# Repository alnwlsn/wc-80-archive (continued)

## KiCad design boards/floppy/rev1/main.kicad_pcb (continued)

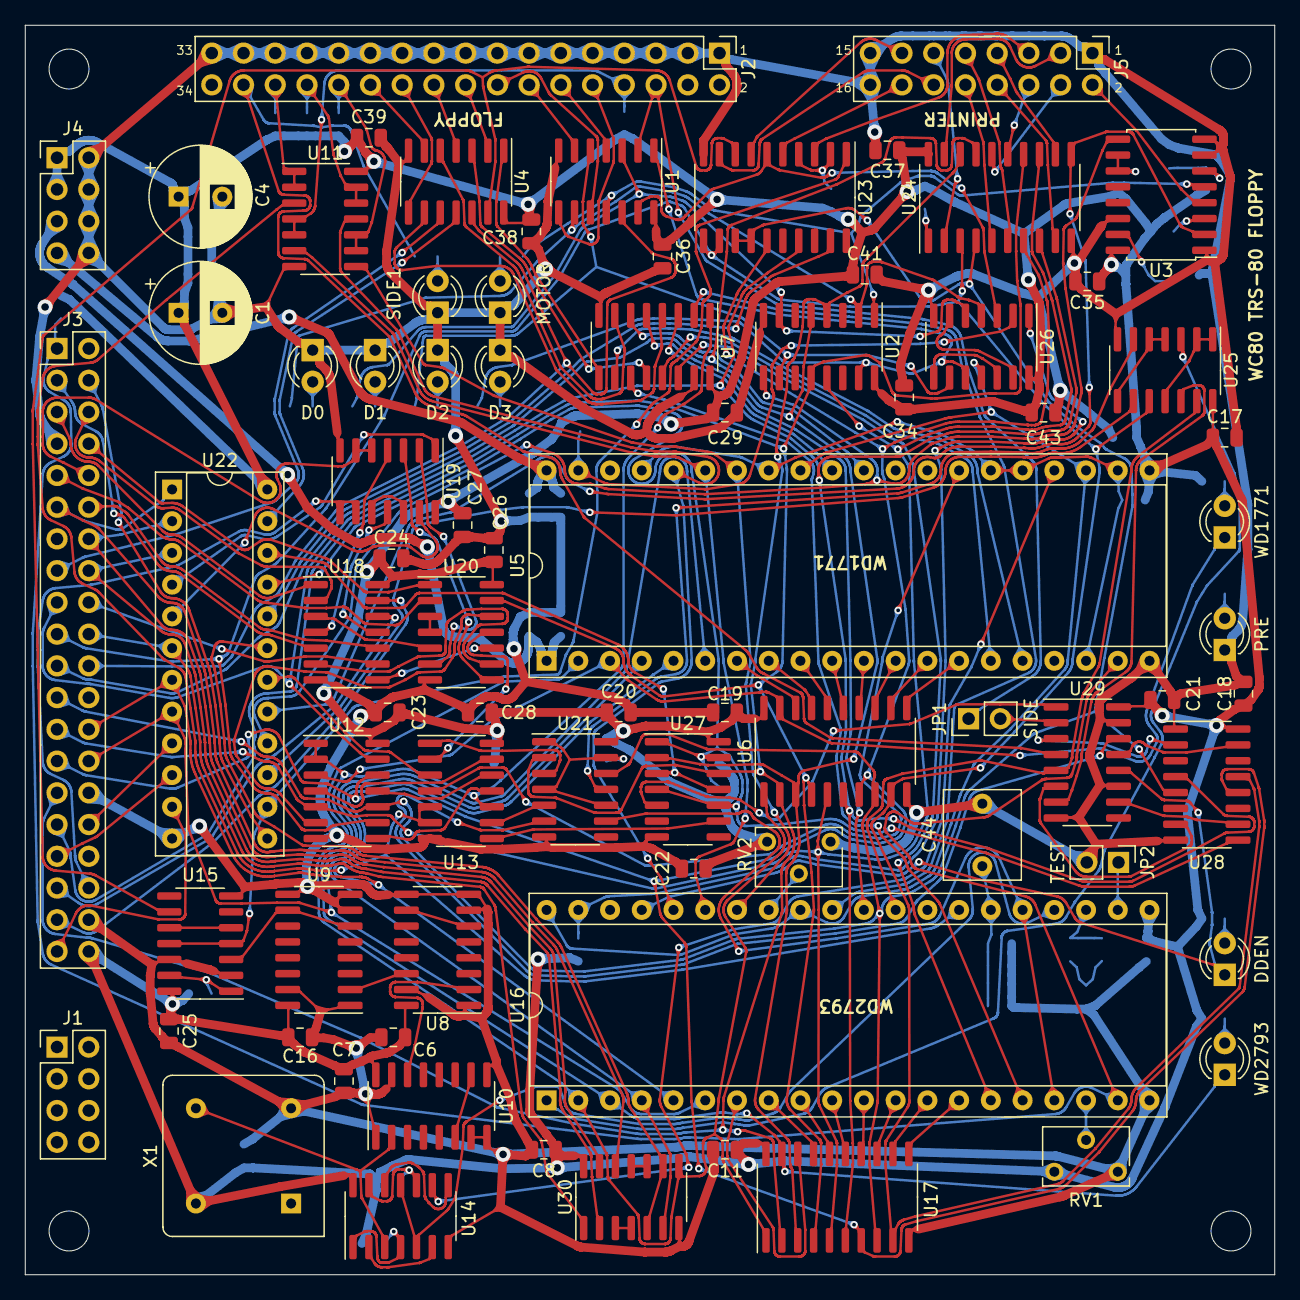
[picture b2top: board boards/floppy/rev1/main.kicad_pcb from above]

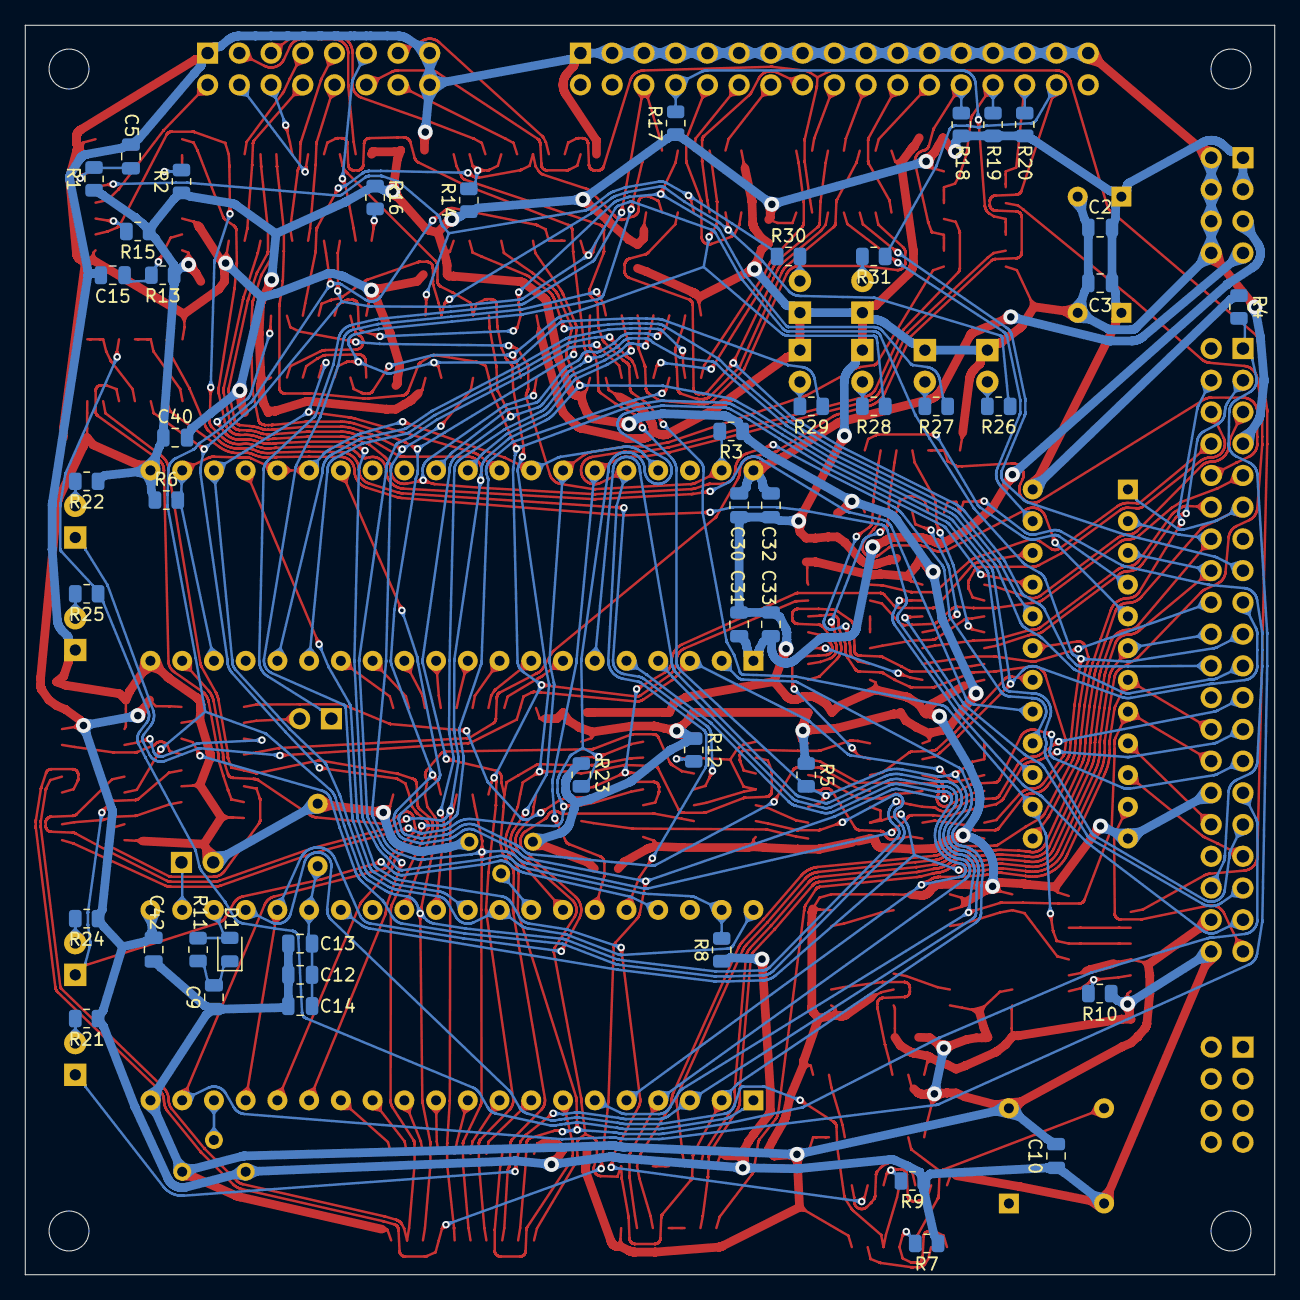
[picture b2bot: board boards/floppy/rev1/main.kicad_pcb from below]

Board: 2 copper layers, 100.0 x 100.0 mm, 130 parts (47 on the bottom side), 196 nets.

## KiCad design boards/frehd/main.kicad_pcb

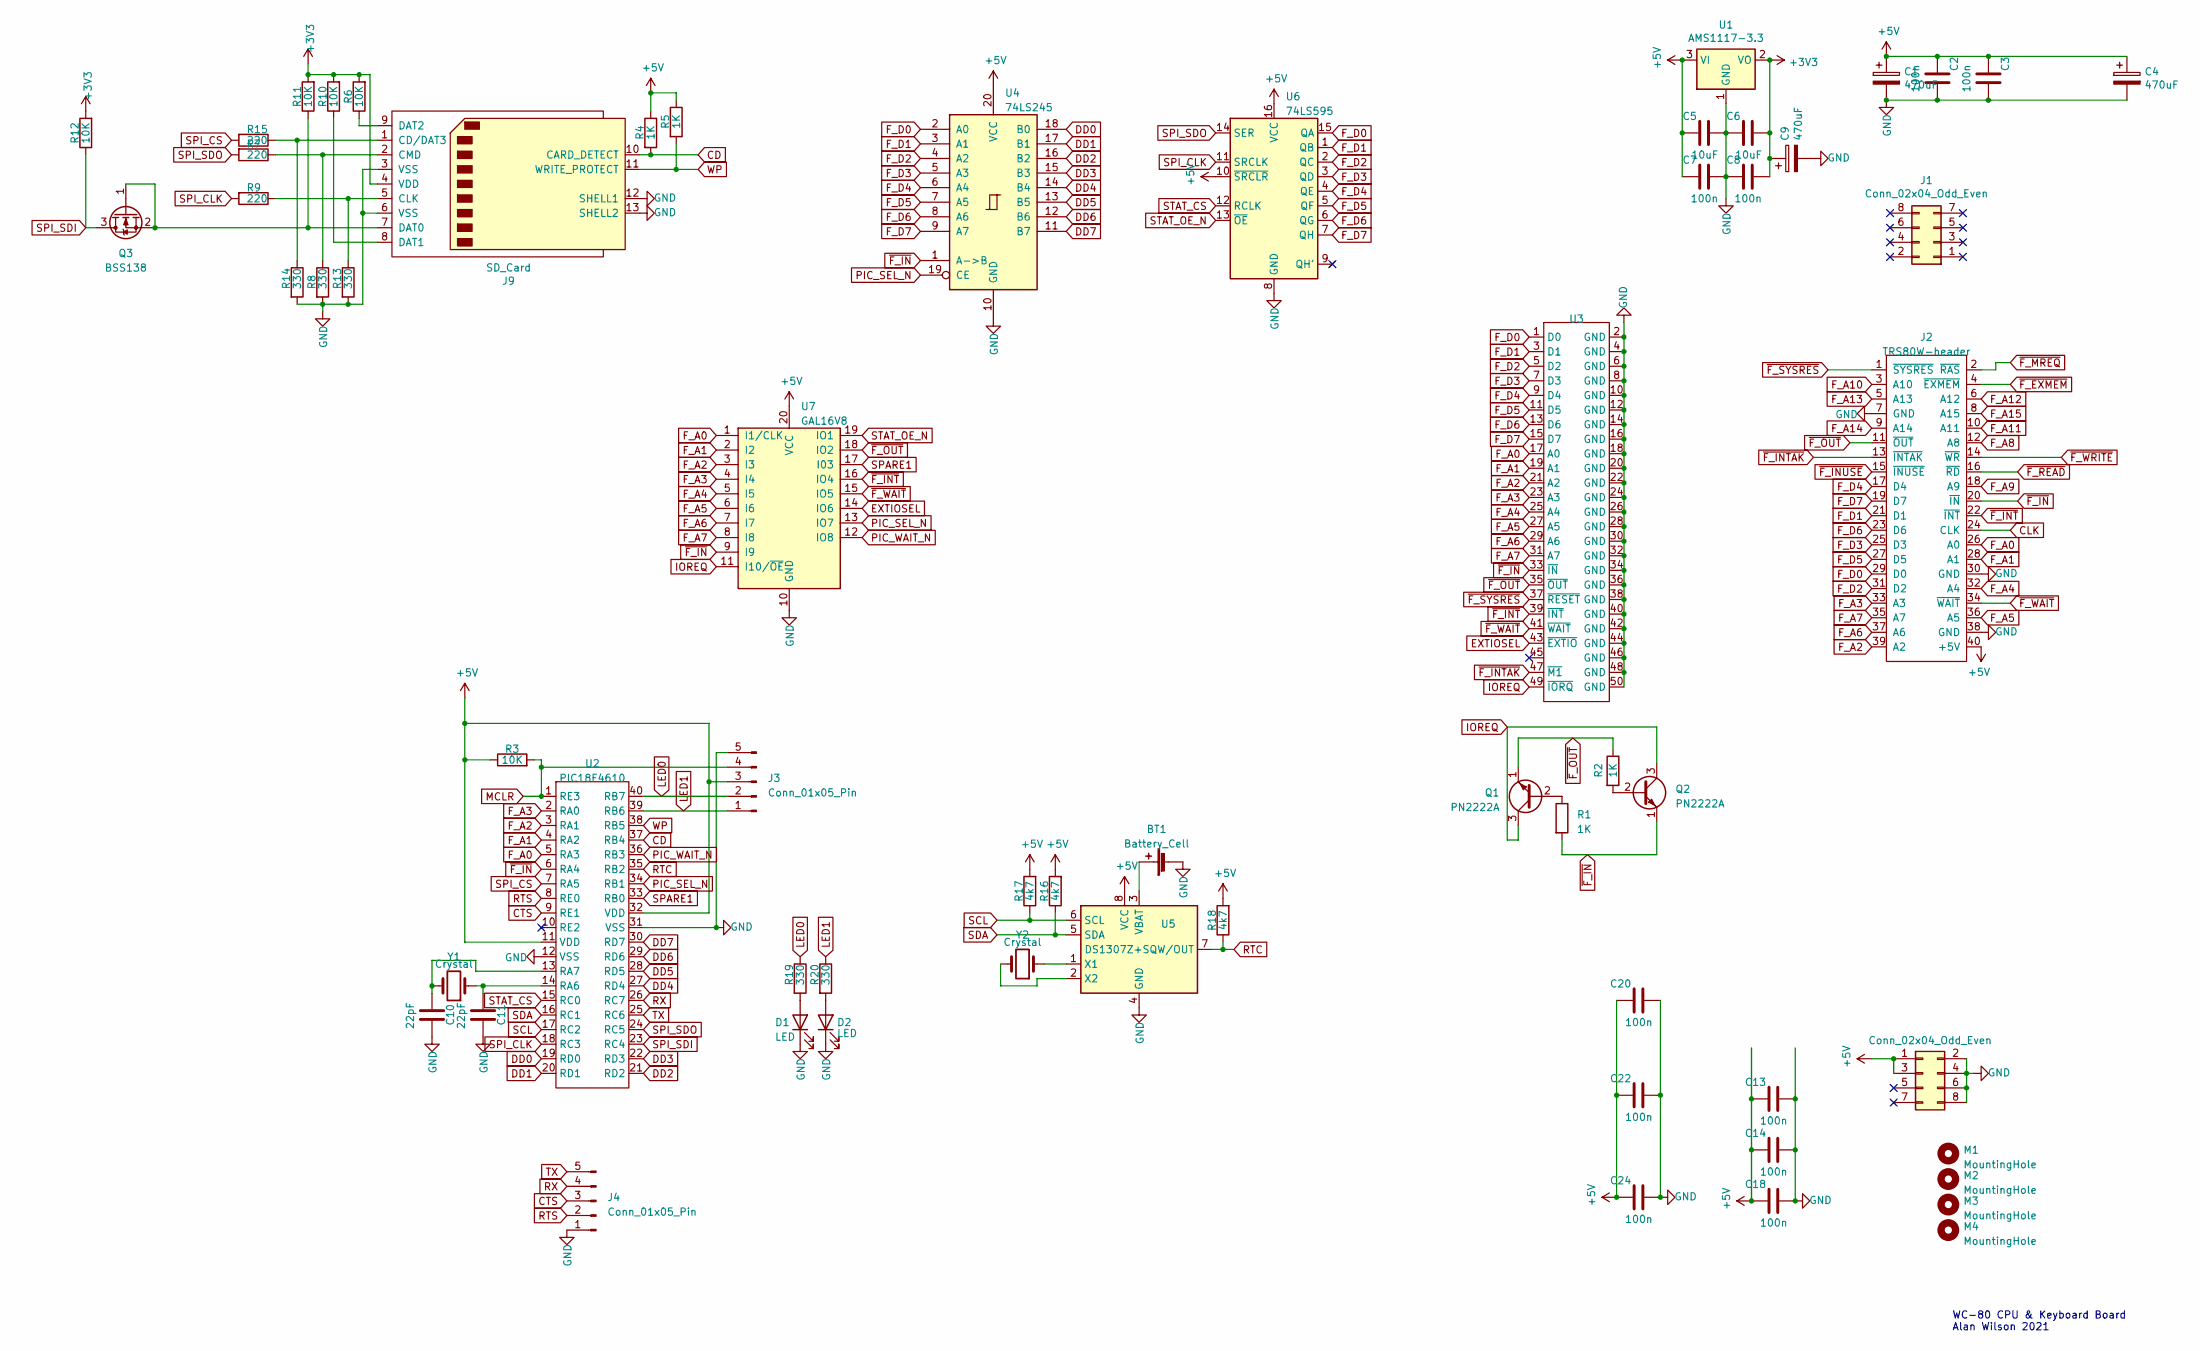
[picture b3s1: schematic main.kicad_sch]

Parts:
BT1: Battery_Cell; BS-01-A4CJ004
C1, C4, C9: 470uF; CP_Radial_D8.0mm_P3.50mm
C2, C3, C7, C8, C13, C14, C18, C20, C22, C24: 100n; C_0805_2012Metric
C5, C6: 10uF; C_0805_2012Metric
C10, C11: 22pF; C_0805_2012Metric
D1, D2: LED; LED_D3.0mm
J1, J5: Conn_02x04_Odd_Even; PinHeader_2x04_P2.54mm_Vertical
J2: TRS80W-header; PinHeader_2x20_P2.54mm_Vertical
J3, J4: Conn_01x05_Pin; PinSocket_1x05_P2.54mm_Vertical
J9: SD_Card; SD_Card_ XUNPU_SD-101
M1, M2, M3, M4: MountingHole; MountingHole_3.2mm_M3_DIN965
Q1, Q2: PN2222A; TO-92_Inline
Q3: BSS138; SOT-23
R1, R2, R4, R5: 1K; R_0805_2012Metric
R3, R6, R10, R11, R12: 10K; R_0805_2012Metric
R7, R9, R15: 220; R_0805_2012Metric
R8, R13, R14, R19, R20: 330; R_0805_2012Metric
R16, R17, R18: 4k7; R_0805_2012Metric
U1: AMS1117-3.3; SOT-223-3_TabPin2
U2: PIC18F4610; DIP-40_W15.24mm_Socket
U3: PinSocket_2x25_P2.54mm_Vertical
U4: 74LS245; SO-20_5.3x12.6mm_P1.27mm
U5: DS1307Z+; SOIC-8_3.9x4.9mm_P1.27mm
U6: 74LS595; SO-16_3.9x9.9mm_P1.27mm
U7: GAL16V8; DIP-20_W7.62mm
Y1: Crystal; Crystal_SMD_HC49-SD
Y2: Crystal; Crystal_AT310_D3.0mm_L10.0mm_Horizontal

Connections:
+3V3: C6.2, C8.2, C9.1, J9.4 (VDD), R6.2, R10.2, R11.2, R12.2, U1.2 (VO)
+5V: C1.1, C2.1, C3.1, C4.1, C5.1, C7.1, C13.1, C14.1, C18.1, C20.1, C22.1, C24.1, J2.40 (+5V), J3.3, J5.1, J5.3, R3.1, R4.1, R5.1, R16.2, R17.2, R18.2, U1.3 (VI), U2.11 (VDD), U2.32 (VDD), U4.20 (VCC), U5.8 (VCC), U6.10 (~SRCLR), U6.16 (VCC), U7.20 (VCC)
CD: J9.10 (CARD_DETECT), R4.2, U2.37 (RB4)
CLK: J2.24 (CLK)
CTS: J4.3, U2.9 (RE1)
DD0: U2.19 (RD0), U4.18 (B0)
DD1: U2.20 (RD1), U4.17 (B1)
DD2: U2.21 (RD2), U4.16 (B2)
DD3: U2.22 (RD3), U4.15 (B3)
DD4: U2.27 (RD4), U4.14 (B4)
DD5: U2.28 (RD5), U4.13 (B5)
DD6: U2.29 (RD6), U4.12 (B6)
DD7: U2.30 (RD7), U4.11 (B7)
EXTIOSEL: U3.43 (~EXTIO), U7.14 (IO6)
F_A0: J2.26 (A0), U2.5 (RA3), U3.17 (A0), U7.1 (I1/CLK)
F_A1: J2.28 (A1), U2.4 (RA2), U3.19 (A1), U7.2 (I2)
F_A2: J2.39 (A2), U2.3 (RA1), U3.21 (A2), U7.3 (I3)
F_A3: J2.33 (A3), U2.2 (RA0), U3.23 (A3), U7.4 (I4)
F_A4: J2.32 (A4), U3.25 (A4), U7.5 (I5)
F_A5: J2.36 (A5), U3.27 (A5), U7.6 (I6)
F_A6: J2.37 (A6), U3.29 (A6), U7.7 (I7)
F_A7: J2.35 (A7), U3.31 (A7), U7.8 (I8)
F_A8: J2.12 (A8)
F_A9: J2.18 (A9)
F_A10: J2.3 (A10)
F_A11: J2.10 (A11)
F_A12: J2.6 (A12)
F_A13: J2.5 (A13)
F_A14: J2.9 (A14)
F_A15: J2.8 (A15)
F_D0: J2.29 (D0), U3.1 (D0), U4.2 (A0), U6.15 (QA)
F_D1: J2.21 (D1), U3.3 (D1), U4.3 (A1), U6.1 (QB)
F_D2: J2.31 (D2), U3.5 (D2), U4.4 (A2), U6.2 (QC)
F_D3: J2.25 (D3), U3.7 (D3), U4.5 (A3), U6.3 (QD)
F_D4: J2.17 (D4), U3.9 (D4), U4.6 (A4), U6.4 (QE)
F_D5: J2.27 (D5), U3.11 (D5), U4.7 (A5), U6.5 (QF)
F_D6: J2.23 (D6), U3.13 (D6), U4.8 (A6), U6.6 (QG)
F_D7: J2.19 (D7), U3.15 (D7), U4.9 (A7), U6.7 (QH)
GND: BT1.2 (-), C1.2, C2.2, C3.2, C4.2, C5.2, C6.1, C7.2, C8.1, C9.2, C10.2, C11.2, C13.2, C14.2, C18.2, C20.2, C22.2, C24.2, D1.1 (K), D2.1 (K), J2.7 (GND), J2.30 (GND), J2.38 (GND), J3.5, J4.1, J5.2, J5.4, J5.6, J5.8, J9.3 (VSS), J9.6 (VSS), J9.12 (SHELL1), J9.13 (SHELL2), R8.2, R13.2, R14.2, U1.1 (GND), U2.12 (VSS), U2.31 (VSS), U3.2 (GND), U3.4 (GND), U3.6 (GND), U3.8 (GND), U3.10 (GND), U3.12 (GND), U3.14 (GND), U3.16 (GND), U3.18 (GND), U3.20 (GND), U3.22 (GND), U3.24 (GND), U3.26 (GND), U3.28 (GND), U3.30 (GND), U3.32 (GND), U3.34 (GND), U3.36 (GND), U3.38 (GND), U3.40 (GND), U3.42 (GND), U3.44 (GND), U3.46 (GND), U3.48 (GND), U3.50 (GND), U4.10 (GND), U5.4 (GND), U6.8 (GND), U7.10 (GND)
IOREQ: Q1.3 (C), Q2.3 (C), U3.49 (~IORQ), U7.11 (I10/~OE)
LED0: J3.2, R19.1, U2.40 (RB7)
LED1: J3.1, R20.1, U2.39 (RB6)
MCLR: J3.4, R3.2, U2.1 (RE3)
unnamed: BT1.1 (+), U5.3 (VBAT)
unnamed: D1.2 (A), R19.2
unnamed: D2.2 (A), R20.2
unnamed: J9.1 (CD/DAT3), R14.1, R15.1
unnamed: J9.5 (CLK), R9.1, R13.1
unnamed: J9.2 (CMD), R7.1, R8.1
unnamed: J9.7 (DAT0), Q3.1 (G), Q3.2 (S), R11.1
unnamed: J9.8 (DAT1), R10.1
unnamed: J9.9 (DAT2), R6.1
unnamed: Q1.2 (B), R1.1
unnamed: Q2.2 (B), R2.2
unnamed: C11.1, U2.14 (RA6), Y1.1
unnamed: C10.1, U2.13 (RA7), Y1.2
unnamed: U5.1 (X1), Y2.1
unnamed: U5.2 (X2), Y2.2
PIC_SEL_N: U2.34 (RB1), U4.19 (CE), U7.13 (IO7)
PIC_WAIT_N: U2.36 (RB3), U7.12 (IO8)
RTC: R18.1, U2.35 (RB2), U5.7 (SQW/OUT)
RTS: J4.2, U2.8 (RE0)
RX: J4.4, U2.26 (RC7)
SCL: R17.1, U2.17 (RC2), U5.6 (SCL)
SDA: R16.1, U2.16 (RC1), U5.5 (SDA)
SPARE1: U2.33 (RB0), U7.17 (I03)
SPI_CLK: R9.2, U2.18 (RC3), U6.11 (SRCLK)
SPI_CS: R15.2, U2.7 (RA5)
SPI_SDI: Q3.3 (D), R12.1, U2.23 (RC4)
SPI_SDO: R7.2, U2.24 (RC5), U6.14 (SER)
STAT_CS: U2.15 (RC0), U6.12 (RCLK)
STAT_OE_N: U6.13 (~OE), U7.19 (IO1)
TX: J4.5, U2.25 (RC6)
WP: J9.11 (WRITE_PROTECT), R5.2, U2.38 (RB5)
~F_EXMEM: J2.4 (~EXMEM)
~F_INTAK: J2.13 (~INTAK), U3.47 (~M1)
~F_INT: J2.22 (~INT), U3.39 (~INT), U7.16 (IO4)
~F_INUSE: J2.15 (~INUSE)
~F_IN: J2.20 (~IN), Q2.1 (E), R1.2, U2.6 (RA4), U3.33 (~IN), U4.1 (A->B), U7.9 (I9)
~F_MREQ: J2.2 (~RAS)
~F_OUT: J2.11 (~OUT), Q1.1 (E), R2.1, U3.35 (~OUT), U7.18 (IO2)
~F_READ: J2.16 (~RD)
~F_SYSRES: J2.1 (~SYSRES), U3.37 (~RESET)
~F_WAIT: J2.34 (~WAIT), U3.41 (~WAIT), U7.15 (IO5)
~F_WRITE: J2.14 (~WR)

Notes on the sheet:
WC-80 CPU & Keyboard Board Alan Wilson 2021

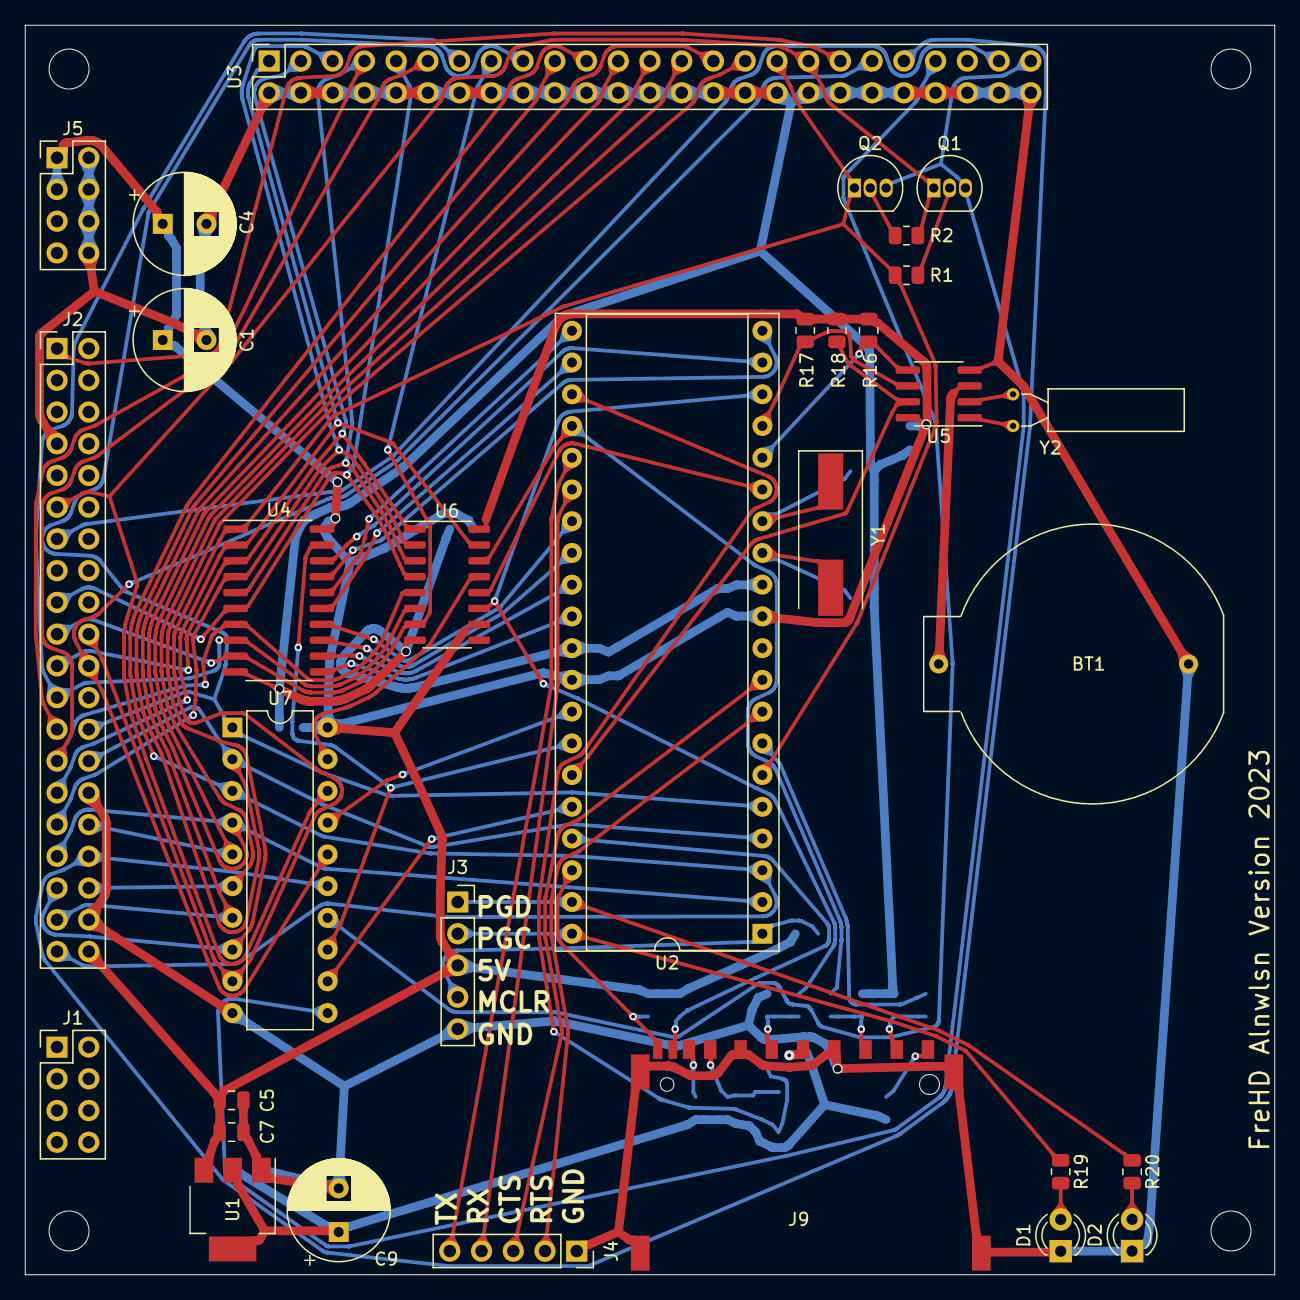
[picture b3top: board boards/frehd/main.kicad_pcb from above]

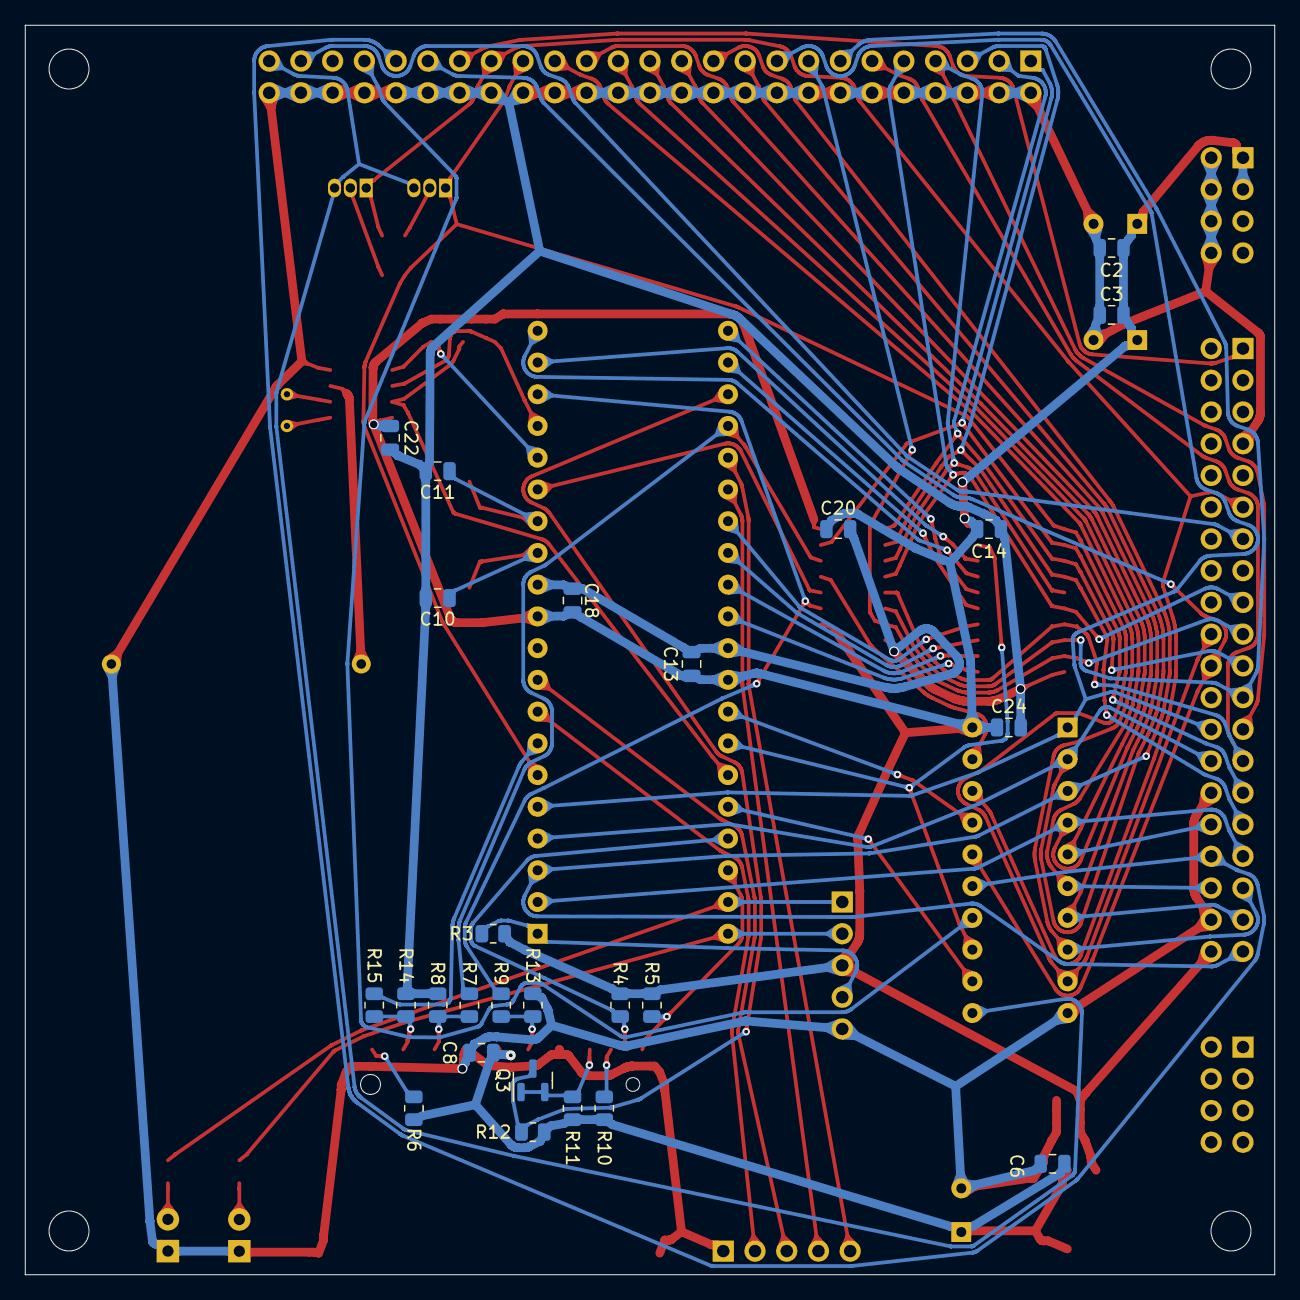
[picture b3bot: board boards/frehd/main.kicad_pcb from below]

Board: 2 copper layers, 100.0 x 100.0 mm, 62 parts (26 on the bottom side), 71 nets.

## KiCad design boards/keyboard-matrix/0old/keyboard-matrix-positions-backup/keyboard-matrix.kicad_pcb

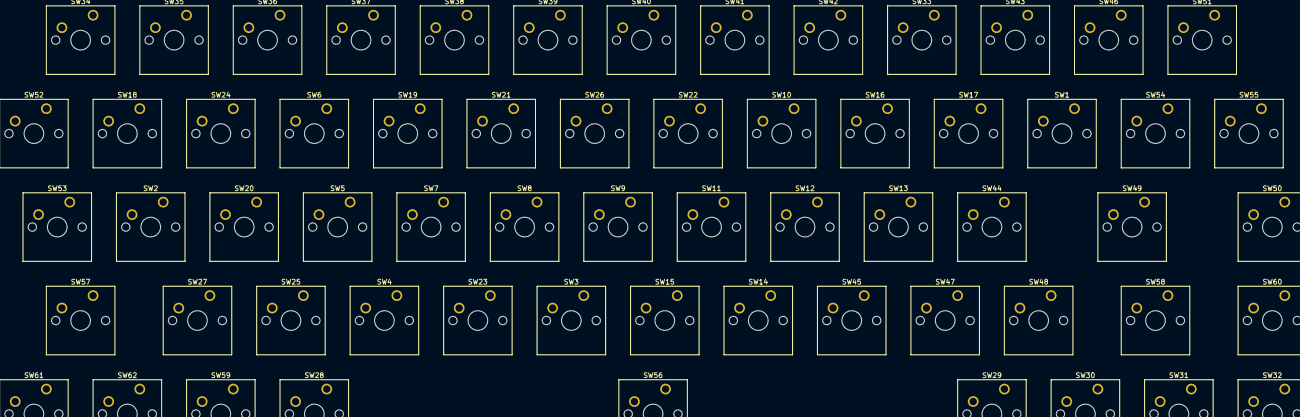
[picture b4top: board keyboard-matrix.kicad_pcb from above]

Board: 2 copper layers, 62 parts (0 on the bottom side), 16 nets, no tracks yet.

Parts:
SW1: @; SW_Cherry_MX_1.00u_PCB
SW2: A; SW_Cherry_MX_1.00u_PCB
SW3: B; SW_Cherry_MX_1.00u_PCB
SW4: C; SW_Cherry_MX_1.00u_PCB
SW5: D; SW_Cherry_MX_1.00u_PCB
SW6: E; SW_Cherry_MX_1.00u_PCB
SW7: F; SW_Cherry_MX_1.00u_PCB
SW8: G; SW_Cherry_MX_1.00u_PCB
SW9: H; SW_Cherry_MX_1.00u_PCB
SW10: I; SW_Cherry_MX_1.00u_PCB
SW11: J; SW_Cherry_MX_1.00u_PCB
SW12: K; SW_Cherry_MX_1.00u_PCB
SW13: L; SW_Cherry_MX_1.00u_PCB
SW14: M; SW_Cherry_MX_1.00u_PCB
SW15: N; SW_Cherry_MX_1.00u_PCB
SW16: O; SW_Cherry_MX_1.00u_PCB
SW17: P; SW_Cherry_MX_1.00u_PCB
SW18: Q; SW_Cherry_MX_1.00u_PCB
SW19: R; SW_Cherry_MX_1.00u_PCB
SW20: S; SW_Cherry_MX_1.00u_PCB
SW21: T; SW_Cherry_MX_1.00u_PCB
SW22: U; SW_Cherry_MX_1.00u_PCB
SW23: V; SW_Cherry_MX_1.00u_PCB
SW24: W; SW_Cherry_MX_1.00u_PCB
SW25: X; SW_Cherry_MX_1.00u_PCB
SW26: Y; SW_Cherry_MX_1.00u_PCB
SW27: Z; SW_Cherry_MX_1.00u_PCB
SW28: Z1; SW_Cherry_MX_1.00u_PCB
SW29: Z2; SW_Cherry_MX_1.00u_PCB
SW30: Z3; SW_Cherry_MX_1.00u_PCB
SW31: Z4; SW_Cherry_MX_1.00u_PCB
SW32: Z5; SW_Cherry_MX_1.00u_PCB
SW33: 0; SW_Cherry_MX_1.00u_PCB
SW34: 1; SW_Cherry_MX_1.00u_PCB
SW35: 2; SW_Cherry_MX_1.00u_PCB
SW36: 3; SW_Cherry_MX_1.00u_PCB
SW37: 4; SW_Cherry_MX_1.00u_PCB
SW38: 5; SW_Cherry_MX_1.00u_PCB
SW39: 6; SW_Cherry_MX_1.00u_PCB
SW40: 7; SW_Cherry_MX_1.00u_PCB
SW41: 8; SW_Cherry_MX_1.00u_PCB
SW42: 9; SW_Cherry_MX_1.00u_PCB
SW43: *; SW_Cherry_MX_1.00u_PCB
SW44: +; SW_Cherry_MX_1.00u_PCB
SW45: <; SW_Cherry_MX_1.00u_PCB
SW46: =; SW_Cherry_MX_1.00u_PCB
SW47: >; SW_Cherry_MX_1.00u_PCB
SW48: ?; SW_Cherry_MX_1.00u_PCB
SW49: Enter; SW_Cherry_MX_1.00u_PCB
SW50: Clear; SW_Cherry_MX_1.00u_PCB
SW51: Break; SW_Cherry_MX_1.00u_PCB
SW52: Up; SW_Cherry_MX_1.00u_PCB
SW53: Down; SW_Cherry_MX_1.00u_PCB
SW54: Left; SW_Cherry_MX_1.00u_PCB
SW55: Right; SW_Cherry_MX_1.00u_PCB
SW56: Space; SW_Cherry_MX_1.00u_PCB
SW57: Shift; SW_Cherry_MX_1.00u_PCB
SW58: R Shift; SW_Cherry_MX_1.00u_PCB
SW59: Z0; SW_Cherry_MX_1.00u_PCB
SW60: Control; SW_Cherry_MX_1.00u_PCB
SW61: NMI; SW_Cherry_MX_1.00u_PCB
SW62: RESET; SW_Cherry_MX_1.00u_PCB

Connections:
unnamed: SW1.1, SW2.1, SW3.1, SW4.1, SW5.1, SW6.1, SW7.1, SW8.1
unnamed: SW1.2, SW9.2, SW17.2, SW25.2, SW33.2, SW41.2, SW49.2, SW57.2
unnamed: SW9.1, SW10.1, SW11.1, SW12.1, SW13.1, SW14.1, SW15.1, SW16.1
unnamed: SW2.2, SW10.2, SW18.2, SW26.2, SW34.2, SW42.2, SW50.2, SW58.2
unnamed: SW3.2, SW11.2, SW19.2, SW27.2, SW35.2, SW43.2, SW51.2, SW59.2
unnamed: SW4.2, SW12.2, SW20.2, SW28.2, SW36.2, SW44.2, SW52.2
unnamed: SW5.2, SW13.2, SW21.2, SW29.2, SW37.2, SW45.2, SW53.2, SW60.2
unnamed: SW6.2, SW14.2, SW22.2, SW30.2, SW38.2, SW46.2, SW54.2
unnamed: SW7.2, SW15.2, SW23.2, SW31.2, SW39.2, SW47.2, SW55.2
unnamed: SW8.2, SW16.2, SW24.2, SW32.2, SW40.2, SW48.2, SW56.2
unnamed: SW17.1, SW18.1, SW19.1, SW20.1, SW21.1, SW22.1, SW23.1, SW24.1
unnamed: SW25.1, SW26.1, SW27.1, SW28.1, SW29.1, SW30.1, SW31.1, SW32.1
unnamed: SW33.1, SW34.1, SW35.1, SW36.1, SW37.1, SW38.1, SW39.1, SW40.1
unnamed: SW41.1, SW42.1, SW43.1, SW44.1, SW45.1, SW46.1, SW47.1, SW48.1
unnamed: SW49.1, SW50.1, SW51.1, SW52.1, SW53.1, SW54.1, SW55.1, SW56.1
unnamed: SW57.1, SW58.1, SW59.1, SW60.1
